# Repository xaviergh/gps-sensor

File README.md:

# gps-sensor

Small geolocated sensing datalogger board for movement sensing.

The design is based on the [Adafruit Feather M0 Adalogger](https://www.adafruit.com/product/2796) and the insights from [PaulZC](https://github.com/PaulZC).

## Main Hardware:

 - MCU: ATSAMD21G18 
 - GPS: uBlox SAM-M8Q 
 - Acc: ADXL345
 - Lipo Connection and Charging
 - Microphone Connections:
[Adafruit I2S MEMS Microphone Breakout - SPH0645LM4H](https://www.adafruit.com/product/3421)
[Adafruit Silicon MEMS Microphone Breakout - SPW2430](https://www.adafruit.com/product/2716)

## Libraries

 - [Adafruit ADXL245](https://learn.adafruit.com/adxl345-digital-accelerometer/overview)
 - [TinyGPS+](https://github.com/mikalhart/TinyGPSPlus)
 - [Arduino Log](https://github.com/thijse/Arduino-Log)
 - [Time](https://github.com/PaulStoffregen/Time)
 - [Arduino Sound](https://github.com/arduino-libraries/ArduinoSound)

## Firmware
The sample Arduino code use the bootloader from the  [Adafruit M0](https://learn.adafruit.com/compiling-m0-atsamd21-bootloader/compile)

## TODO
Hardware
 - Improve GPS fix time

Software
 - Improve Microphone reading accuracy
 - Dual microphone noise cancelling

> Written with [StackEdit](https://stackedit.io/).

<!--stackedit_data:
eyJoaXN0b3J5IjpbLTE0MDMwNTUxNzYsLTE0ODEyNjQ0NTksLT
EwNjQ0NzYzNzgsLTE5NTU5NTM1NTFdfQ==
-->

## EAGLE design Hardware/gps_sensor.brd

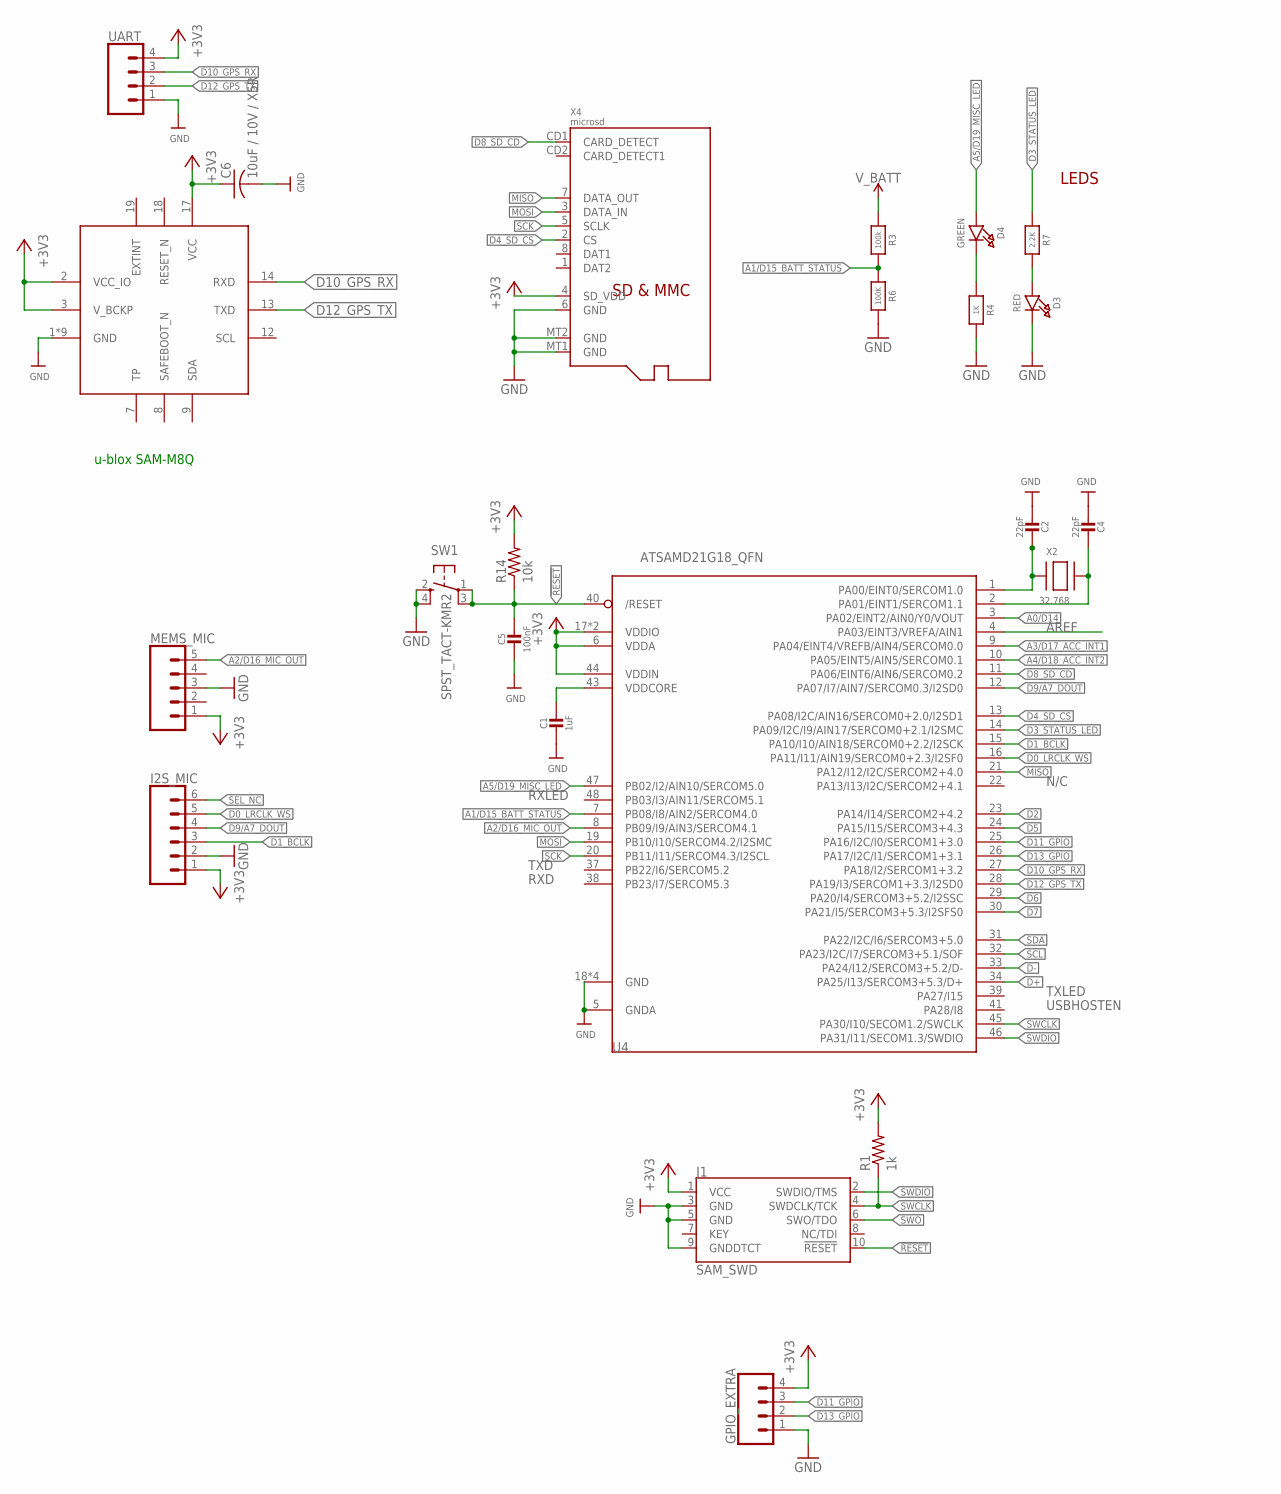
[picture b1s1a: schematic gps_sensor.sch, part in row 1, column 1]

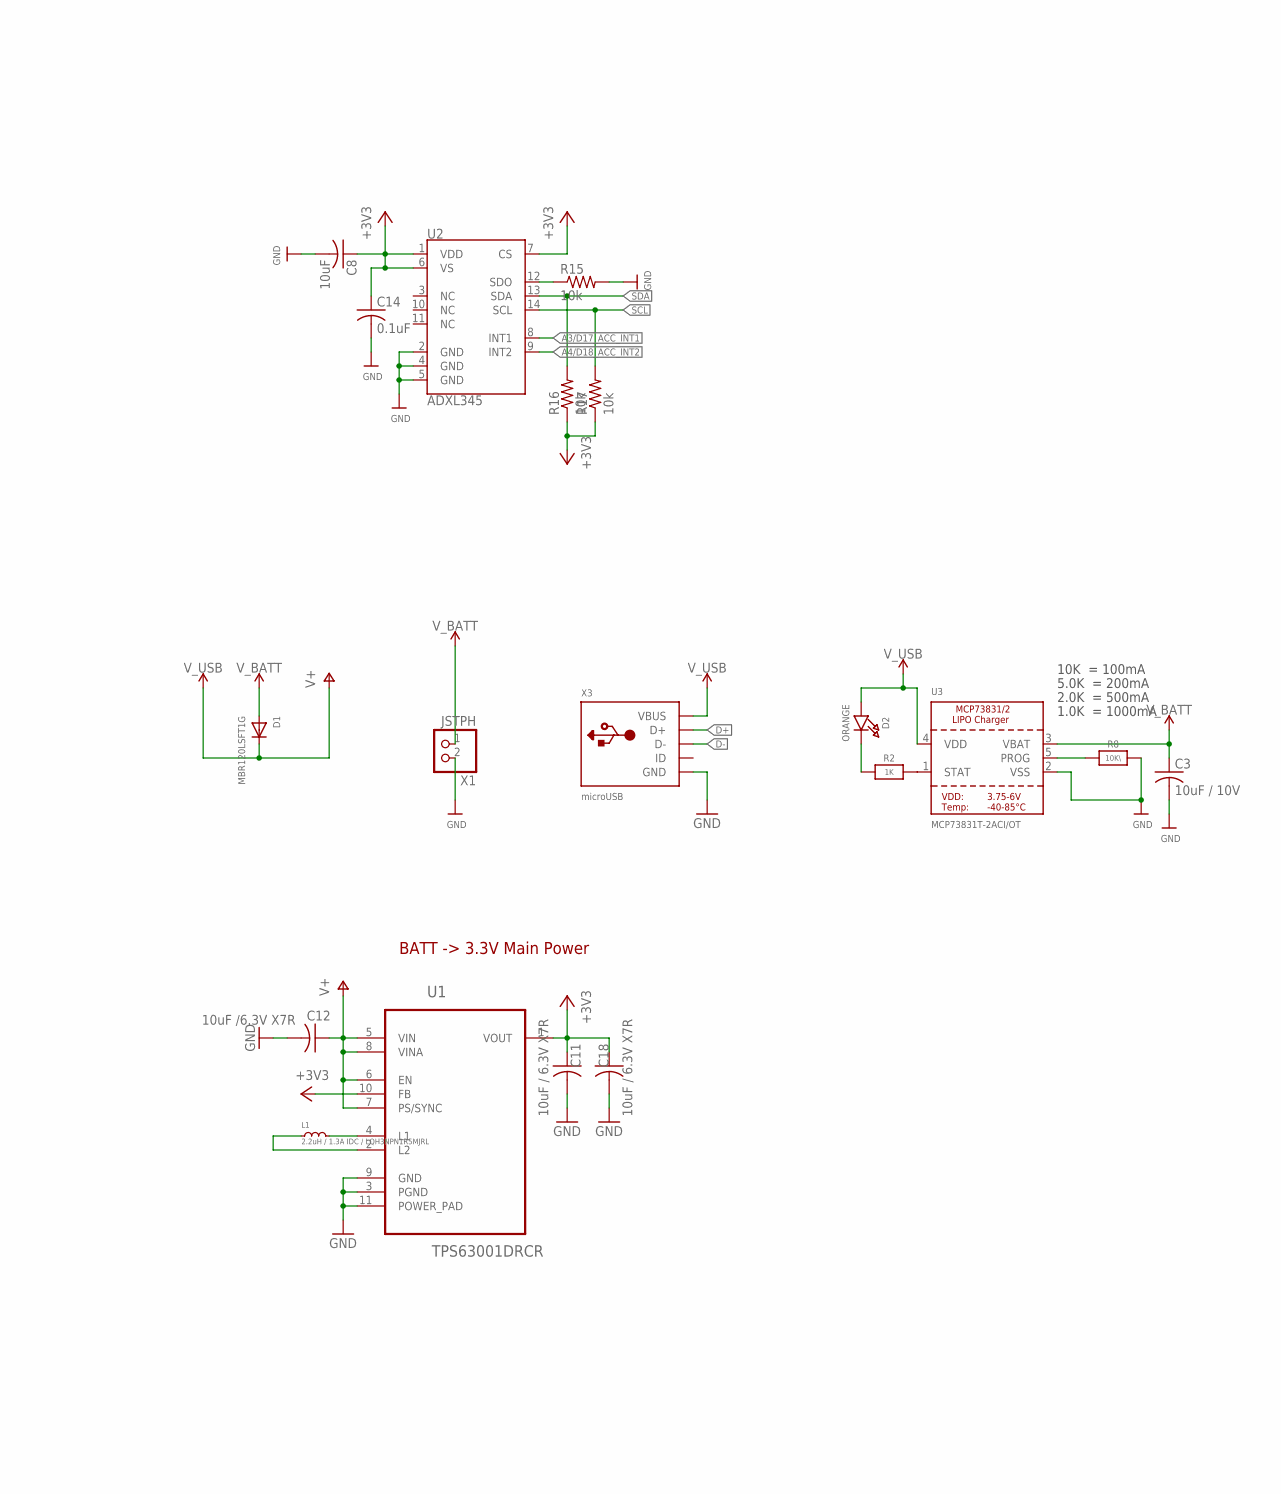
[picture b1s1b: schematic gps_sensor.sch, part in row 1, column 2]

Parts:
C1: 1uF; 0603-NO
C2, C4: 22pF; 0603-NO
C3: 10uF / 10V; C0603
C5: 100nF; 0603-NO
C6: 10uF / 10V / X5R; C0603
C8: 10uF; C0603
C11, C18: 10uF / 6.3V X7R; C0603
C12: 10uF /6.3V X7R; C0603
C14: 0.1uF; C0603
D1: MBR120LSFT1G; SOD-123FL
D2: ORANGE; CHIPLED_0805_NOOUTLINE
D3: RED; CHIPLED_0805_NOOUTLINE
D4: GREEN; CHIPLED_0805_NOOUTLINE
GPIO_EXTRA: CONN_04; 1X04
I2S_MIC: CONN_06NO_SILK_NO_POP; 1X06_NO_SILK
J1: SAM_SWD; SAMTECH_FTSH-105-01
L1: 2.2uH / 1.3A IDC / LQH3NPN1R5MJRL; LQH3NP_M0
MEMS_MIC: CONN_05; 1X05
R1: 1k; R0603
R2, R4: 1K; 0603-NO
R3: 100k; 0603-NO
R6: 100K; 0603-NO
R7: 2.2K; 0603-NO
R8: 10K\; 0603-NO
R14, R15, R16, R17: 10k; R0603
SW1: SPST_TACT-KMR2; KMR2
U1: TPS63001DRCR; SON50P300X300X100-11N
U2: ADXL345; LGA-14
U3: MCP73831T-2ACI/OT; SOT23-5
U4: ATSAMD21G18_QFN; TQFN48_7MM
U5: SAM-M8Q
UART: CONN_041X04_NO_SILK; 1X04_NO_SILK
X1: JSTPH; JST-PH-2-SMT-RA
X2: 32.768; XTAL3215
X3: microUSB; 4UCONN_20329_V2
X4: microsd; MICROSD

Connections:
!RESET: C5.1, J1.10 (!RESET), R14.1, SW1.1, SW1.3 (P1), U4.40 (/RESET)
+3V3: C6.1, C8.1, C11.1, C14.1, C18.1, GPIO_EXTRA.4, I2S_MIC.1, J1.1 (VCC), MEMS_MIC.1, R1.2, R14.2, R16.1, R17.1, U1.1 (VOUT), U1.10 (FB), U2.1 (VDD), U2.6 (VS), U2.7 (CS), U4.6 (VDDA), U4.17 (VDDIO), U4.36 (VDDIO), U4.44 (VDDIN), U5.2 (VCC_IO), U5.3 (V_BCKP), U5.17 (VCC), UART.4, X4.4 (SD_VDD)
A0/D14: U4.3 (PA02/EINT2/AIN0/Y0/VOUT)
A1/D15_BATT_STATUS: R3.2, R6.1, U4.7 (PB08/I8/AIN2/SERCOM4.0)
A2/D16_MIC_OUT: MEMS_MIC.5, U4.8 (PB09/I9/AIN3/SERCOM4.1)
A3/D17_ACC_INT1: U2.8 (INT1), U4.9 (PA04/EINT4/VREFB/AIN4/SERCOM0.0)
A4/D18_ACC_INT2: U2.9 (INT2), U4.10 (PA05/EINT5/AIN5/SERCOM0.1)
A5/D19_MISC_LED: D4.A, U4.47 (PB02/I2/AIN10/SERCOM5.0)
AREF: U4.4 (PA03/EINT3/VREFA/AIN1)
D0_LRCLK_WS: I2S_MIC.5, U4.16 (PA11/I11/AIN19/SERCOM0+2.3/I2SF0)
D1_BCLK: I2S_MIC.3, U4.15 (PA10/I10/AIN18/SERCOM0+2.2/I2SCK)
D2: U4.23 (PA14/I14/SERCOM2+4.2)
D3_STATUS_LED: R7.1, U4.14 (PA09/I2C/I9/AIN17/SERCOM0+2.1/I2SMC)
D4_SD_CS: U4.13 (PA08/I2C/AIN16/SERCOM0+2.0/I2SD1), X4.2 (CS)
D5: U4.24 (PA15/I15/SERCOM3+4.3)
D6: U4.29 (PA20/I4/SERCOM3+5.2/I2SSC)
D7: U4.30 (PA21/I5/SERCOM3+5.3/I2SFS0)
D8_SD_CD: U4.11 (PA06/EINT6/AIN6/SERCOM0.2), X4.CD1 (CARD_DETECT)
D9/A7_DOUT: I2S_MIC.4, U4.12 (PA07/I7/AIN7/SERCOM0.3/I2SD0)
D10_GPS_RX: U4.27 (PA18/I2/SERCOM1+3.2), U5.14 (RXD), UART.3
D11_GPIO: GPIO_EXTRA.3, U4.25 (PA16/I2C/I0/SERCOM1+3.0)
D12_GPS_TX: U4.28 (PA19/I3/SERCOM1+3.3/I2SD0), U5.13 (TXD), UART.2
D13_GPIO: GPIO_EXTRA.2, U4.26 (PA17/I2C/I1/SERCOM1+3.1)
D+: U4.34 (PA25/I13/SERCOM3+5.3/D+), X3.D+
D-: U4.33 (PA24/I12/SERCOM3+5.2/D-), X3.D-
GND: C1.2, C2.2, C3.2, C4.2, C5.2, C6.2, C8.2, C11.2, C12.2, C14.2, C18.2, D3.C, GPIO_EXTRA.1, I2S_MIC.2, J1.3 (GND), J1.5 (GND), J1.9 (GNDDTCT), MEMS_MIC.3, R4.2, R6.2, R8.2, R15.2, SW1.2 (S), SW1.4 (S1), U1.3 (PGND), U1.9 (GND), U1.11 (POWER_PAD), U2.2 (GND), U2.4 (GND), U2.5 (GND), U3.2 (VSS), U4.5 (GNDA), U4.18 (GND), U4.35 (GND), U4.42 (GND), U4.THERMAL (GND), U5.1 (GND), U5.4 (GND), U5.5 (GND), U5.6 (GND), U5.10 (GND), U5.11 (GND), U5.15 (GND), U5.16 (GND), U5.20 (GND), UART.1, X1.2 (1), X3.BASE@1 (GND), X3.BASE@2 (GND), X3.GND, X3.SPRT@1 (GND), X3.SPRT@2 (GND), X3.SPRT@3 (GND), X3.SPRT@4 (GND), X4.6 (GND), X4.MT1 (GND), X4.MT2 (GND)
MISO: U4.21 (PA12/I12/I2C/SERCOM2+4.0), X4.7 (DATA_OUT)
MOSI: U4.19 (PB10/I10/SERCOM4.2/I2SMC), X4.3 (DATA_IN)
unnamed: D2.C, R2.1
unnamed: D3.A, R7.2
unnamed: R2.2, U3.1 (STAT)
unnamed: R8.1, U3.5 (PROG)
unnamed: C2.1, U4.1 (PA00/EINT0/SERCOM1.0), X2.P$1
unnamed: D4.C, R4.1
unnamed: C4.1, U4.2 (PA01/EINT1/SERCOM1.1), X2.P$2
unnamed: L1.2, U1.4 (L1)
unnamed: L1.1, U1.2 (L2)
unnamed: R15.1, U2.12 (SDO)
SCK: U4.20 (PB11/I11/SERCOM4.3/I2SCL), X4.5 (SCLK)
SCL: R17.2, U2.14 (SCL), U4.32 (PA23/I2C/I7/SERCOM3+5.1/SOF)
SDA: R16.2, U2.13 (SDA), U4.31 (PA22/I2C/I6/SERCOM3+5.0)
SEL_NC: I2S_MIC.6
SWCLK: J1.4 (SWDCLK/TCK), R1.1, U4.45 (PA30/I10/SECOM1.2/SWCLK)
SWDIO: J1.2 (SWDIO/TMS), U4.46 (PA31/I11/SECOM1.3/SWDIO)
SWO: J1.6 (SWO/TDO)
V+: C12.1, D1.C, D2.A, U1.5 (VIN), U1.6 (EN), U1.7 (PS/SYNC), U1.8 (VINA), U3.4 (VDD), X3.VBUS
VDDCORE: C1.1, U4.43 (VDDCORE)
V_BATT: C3.1, D1.A, R3.1, U3.3 (VBAT), X1.1 (2)

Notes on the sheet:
10K = 100mA
5.0K = 200mA
2.0K = 500mA
1.0K = 1000mA
N/C
TXLED
USBHOSTEN
RXLED
TXD
RXD
LEDS
u-blox SAM-M8Q
BATT -> 3.3V Main Power

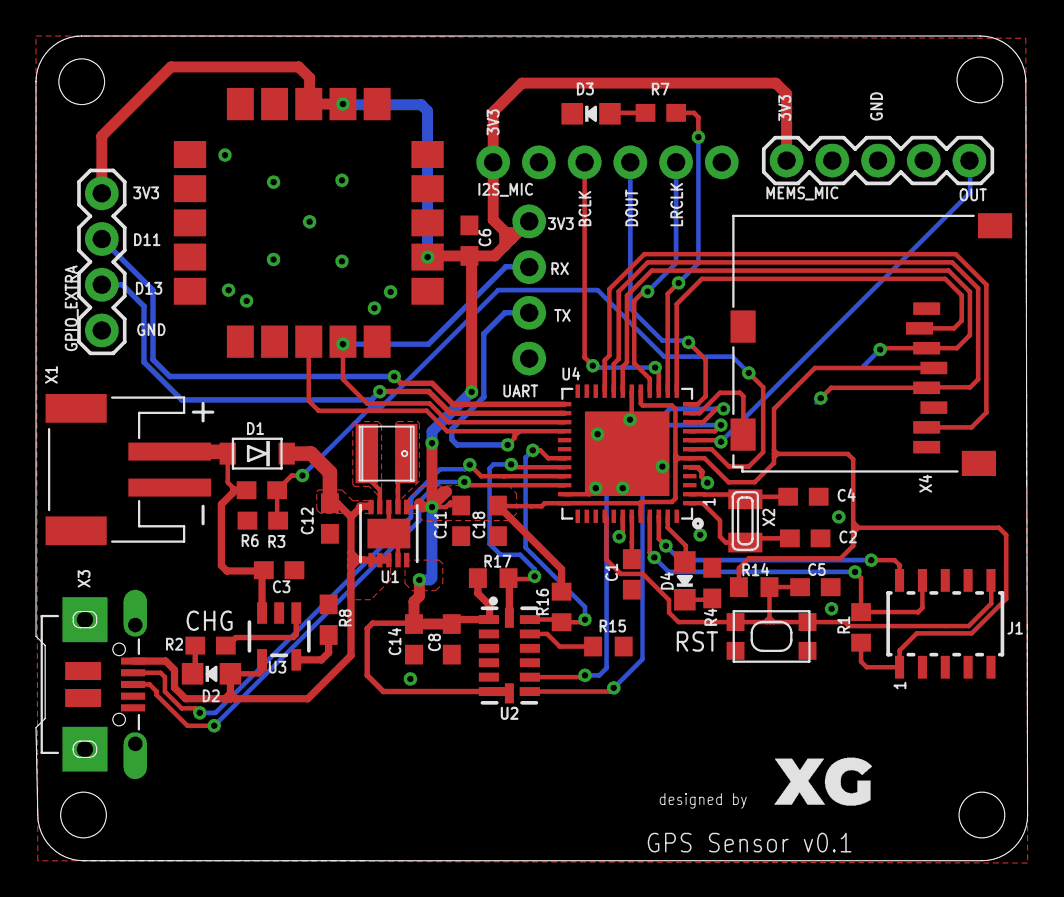
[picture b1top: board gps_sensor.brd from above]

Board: 2 copper layers, 55.1 x 45.8 mm, 42 parts (0 on the bottom side), 40 nets.

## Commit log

2018-12-28 Initial commit with first working files
2018-12-28 README.md updated from https://stackedit.io/
2018-12-29 added PCB image

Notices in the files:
parts and their libraries:
microbuilder: This work is placed in the public domain, and may be freely used for commercial and non-commercial work with the following conditions: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
SparkFun-Connectors: Licensing: Creative Commons ShareAlike 4.0 International - https://creativecommons.org/licenses/by-sa/4.0
